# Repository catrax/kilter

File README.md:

# kilter
A compact multimode eurorack filter with MS-20 style resonance.
Filter core and resonance based on [René Schmitz' MS-20 schematic](https://www.schmitzbits.de/ms20.html).

# Features
- Voltage controlled filter with 4 simultaneous outputs:
	- 1-pole high pass
	- 2-pole low pass
	- 2-pole band pass (it's kind of an afterthought and needs to be improved, but it sounds okay)
	- 2-pole notch with adjustable depth (via trimmer on back)
- Two frequency CV inputs, one with an attenuverter
- Voltage controlled resonance with adjustable drive
- Two inputs with linear cross-fade
- 6HP

# Specifications
TODO: HP, power requirements, depth, input/output impedances and voltage ranges

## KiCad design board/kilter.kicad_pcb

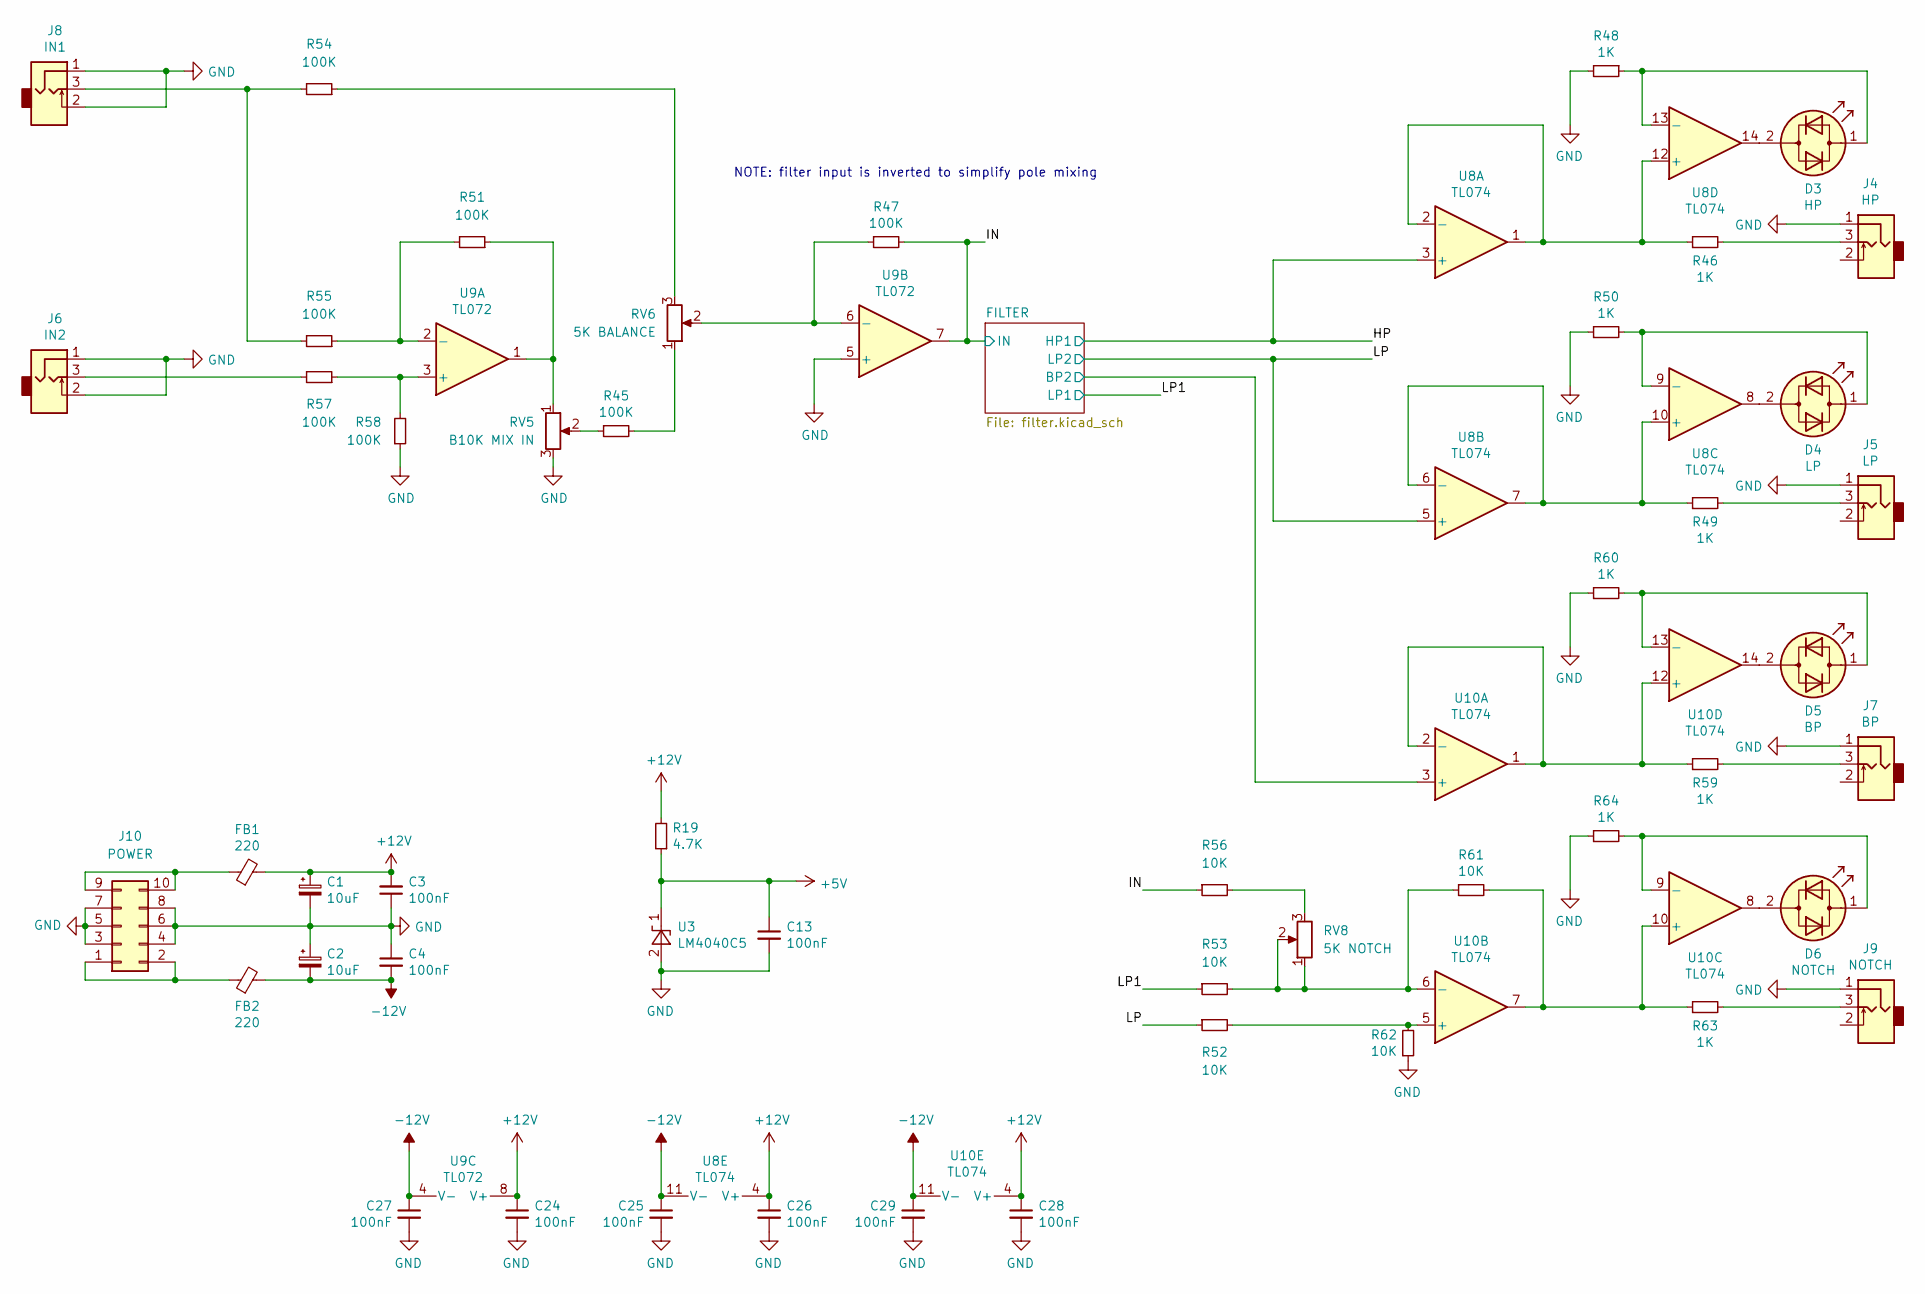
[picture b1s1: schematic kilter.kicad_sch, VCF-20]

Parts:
C1, C2: 10uF; CP_Elec_5x5.3; LCSC C178621
C3, C4, C13, C24, C25, C26, C27, C28, C29: 100nF; C_0603_1608Metric; LCSC C14663
D3: HP; LED_D3.0mm_Clear
D4: LP; LED_D3.0mm_Clear
D5: BP; LED_D3.0mm_Clear
D6: NOTCH; LED_D3.0mm_Clear
FB1, FB2: 220; R_0603_1608Metric; LCSC C88988
J4: HP; PJ301M
J5: LP; PJ301M
J6: IN2; PJ301M
J7: BP; PJ301M
J8: IN1; PJ301M
J9: NOTCH; PJ301M
J10: POWER; IDC-Header_2x05_P2.54mm_Vertical
R19: 4.7K; R_0603_1608Metric; LCSC C23162
R45, R47, R51, R54, R55, R57, R58: 100K; R_0603_1608Metric; LCSC C25803
R46, R48, R49, R50, R59, R60, R63, R64: 1K; R_0603_1608Metric; LCSC C21190
R52, R53, R56, R61, R62: 10K; R_0603_1608Metric; LCSC C25804
RV5: B10K MIX IN; Potentiometer_SongHuei_RD0904N-L25-KQ_Single_Vertical
RV6: 5K BALANCE; Potentiometer_Bourns_TC33X_Vertical; LCSC C719177
RV8: 5K NOTCH; Potentiometer_Bourns_TC33X_Vertical; LCSC C719177
U3: LM4040C5; SOT-23; LCSC C156291
U8, U10: TL074; TSSOP-14_4.4x5mm_P0.65mm; LCSC C96507
U9: TL072; TSSOP-8_4.4x3mm_P0.65mm; LCSC C90748

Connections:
+5V: C13.1, R19.1, U3.1 (K); also elsewhere on the board
+12V: C1.1, C3.2, C24.1, C26.1, C28.1, FB1.2, R19.2, U8.4 (V+), U9.8 (V+), U10.4 (V+); also elsewhere on the board
-12V: C2.2, C4.2, C25.1, C27.1, C29.1, FB2.2, U8.11 (V-), U9.4 (V-), U10.11 (V-); also elsewhere on the board
/FILTER/BP2: U10.3 (+); also elsewhere on the board
/HP: U8.3 (+); also elsewhere on the board
/IN: R47.2, R56.1, U9.7; also elsewhere on the board
/LP: R52.1, U8.5 (+); also elsewhere on the board
/LP1: R53.1; also elsewhere on the board
GND: C1.2, C2.1, C3.1, C4.1, C13.2, C24.2, C25.2, C26.2, C27.2, C28.2, C29.2, J4.1, J5.1, J6.1, J6.2, J7.1, J8.1, J8.2, J9.1, J10.3, J10.4, J10.5, J10.6, J10.7, J10.8, R48.2, R50.1, R58.1, R60.1, R62.1, R64.1, RV5.3, U3.2 (A), U9.5 (+); also elsewhere on the board
unnamed: D3.1 (KA), R48.1, U8.13 (-)
unnamed: D3.2 (AK), U8.14
unnamed: D4.1 (KA), R50.2, U8.9 (-)
unnamed: D4.2 (AK), U8.8
unnamed: D5.1 (KA), R60.2, U10.13 (-)
unnamed: D5.2 (AK), U10.14
unnamed: D6.1 (KA), R64.2, U10.9 (-)
unnamed: D6.2 (AK), U10.8
unnamed: FB1.1, J10.9, J10.10
unnamed: FB2.1, J10.1, J10.2
unnamed: J8.3, R54.2, R55.2
unnamed: J4.3, R46.2
unnamed: J6.3, R57.2
unnamed: J5.3, R49.2
unnamed: J7.3, R59.2
unnamed: J9.3, R63.2
unnamed: R51.1, RV5.1, U9.1
unnamed: R51.2, R55.1, U9.2 (-)
unnamed: R47.1, RV6.2, U9.6 (-)
unnamed: R46.1, U8.1, U8.2 (-), U8.12 (+)
unnamed: R57.1, R58.2, U9.3 (+)
unnamed: R45.1, RV5.2
unnamed: R45.2, RV6.1
unnamed: R49.1, U8.6 (-), U8.7, U8.10 (+)
unnamed: R59.1, U10.1, U10.2 (-), U10.12 (+)
unnamed: R53.2, R61.1, RV8.1, RV8.2, U10.6 (-)
unnamed: R61.2, R63.1, U10.7, U10.10 (+)
unnamed: R52.2, R62.2, U10.5 (+)
unnamed: R54.1, RV6.3
unnamed: R56.2, RV8.3

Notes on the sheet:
NOTE: filter input is inverted to simplify pole mixing

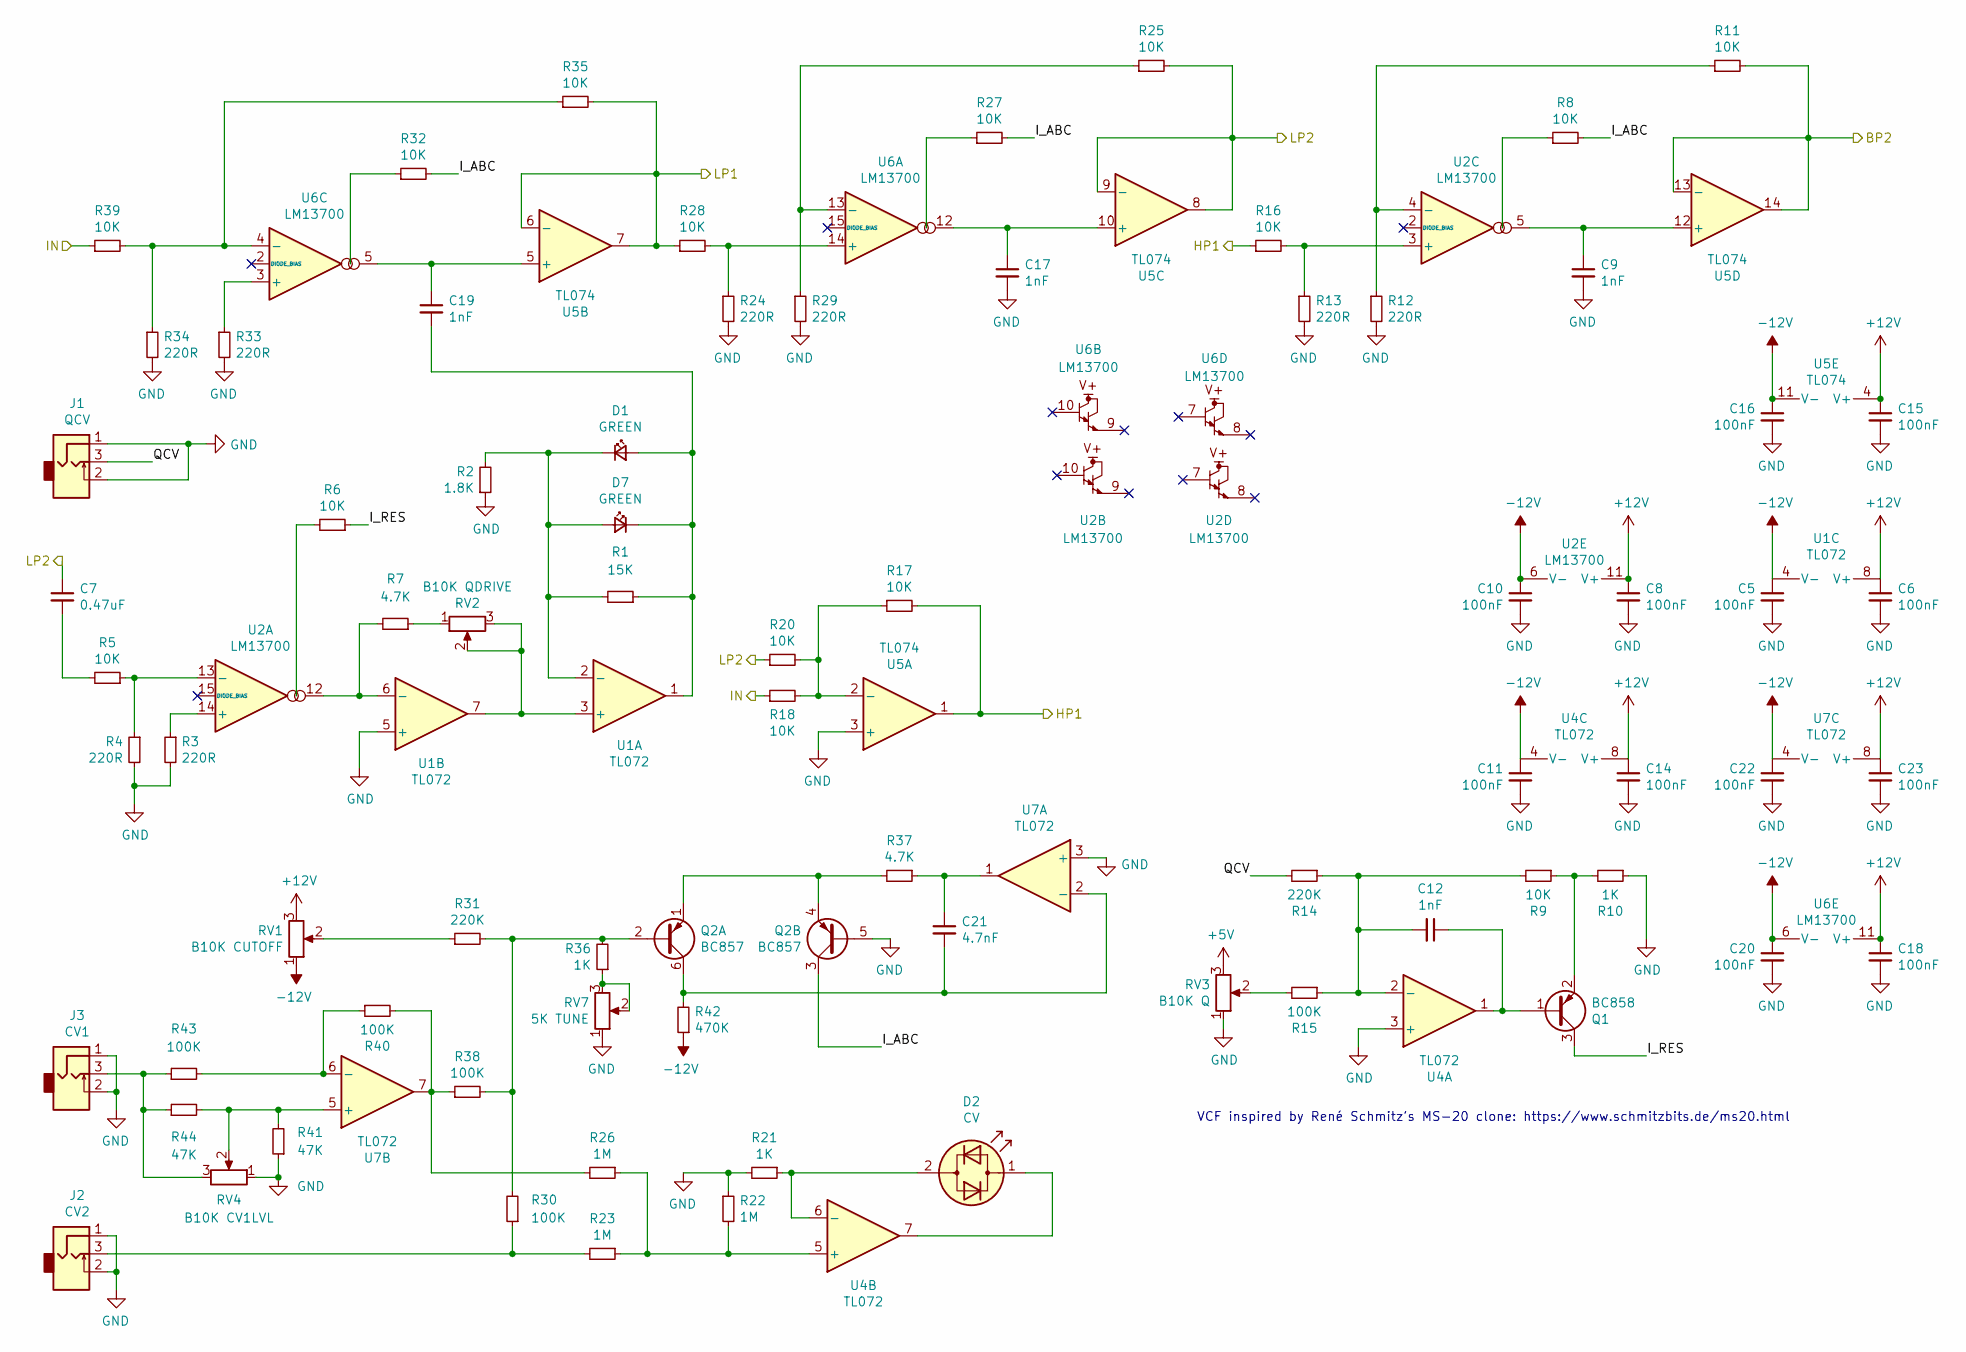
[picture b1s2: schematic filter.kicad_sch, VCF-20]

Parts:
C5, C6, C8, C10, C11, C14, C15, C16, C18, C20, C22, C23: 100nF; C_0603_1608Metric; LCSC C14663
C7: 0.47uF; C_0603_1608Metric; LCSC C1623
C9, C12, C17, C19: 1nF; C_0603_1608Metric; LCSC C1588
C21: 4.7nF; C_0603_1608Metric; LCSC C338071
D1, D7: GREEN; LED_D3.0mm
D2: CV; LED_D3.0mm_Clear
J1: QCV; PJ301M
J2: CV2; PJ301M
J3: CV1; PJ301M
Q1: BC858; SOT-23; LCSC C596216
Q2: BC857; SOT-363_SC-70-6; LCSC C105887
R1: 15K; R_0603_1608Metric; LCSC C22809
R2: 1.8K; R_0603_1608Metric; LCSC C4177
R3, R4, R12, R13, R24, R29, R33, R34: 220R; R_0603_1608Metric; LCSC C22962
R5, R6, R8, R9, R11, R16, R17, R18, R20, R25, R27, R28, R32, R35, R39: 10K; R_0603_1608Metric; LCSC C25804
R7, R37: 4.7K; R_0603_1608Metric; LCSC C23162
R10, R21, R36: 1K; R_0603_1608Metric; LCSC C21190
R14, R31: 220K; R_0603_1608Metric; LCSC C22961
R15, R30, R38, R40, R43: 100K; R_0603_1608Metric; LCSC C25803
R22, R23, R26: 1M; R_0603_1608Metric; LCSC C22935
R41, R44: 47K; R_0603_1608Metric; LCSC C25819
R42: 470K; R_0603_1608Metric; LCSC C23178
RV1: B10K CUTOFF; Potentiometer_Alpha_RD901F-40-00D_Single_Vertical
RV2: B10K QDRIVE; Potentiometer_SongHuei_RD0904N-L25-KQ_Single_Vertical
RV3: B10K Q; Potentiometer_Alpha_RD901F-40-00D_Single_Vertical
RV4: B10K CV1LVL; Potentiometer_Alpha_RD901F-40-00D_Single_Vertical
RV7: 5K TUNE; Potentiometer_Bourns_TC33X_Vertical; LCSC C719177
U1, U4, U7: TL072; TSSOP-8_4.4x3mm_P0.65mm; LCSC C90748
U2, U6: LM13700; SOIC-16_3.9x9.9mm_P1.27mm; LCSC C174050
U5: TL074; TSSOP-14_4.4x5mm_P0.65mm; LCSC C96507

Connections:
+5V: RV3.3; also elsewhere on the board
+12V: C6.1, C8.1, C14.1, C15.1, C18.1, C23.1, RV1.3, U1.8 (V+), U2.11 (V+), U4.8 (V+), U5.4 (V+), U6.11 (V+), U7.8 (V+); also elsewhere on the board
-12V: C5.1, C10.1, C11.1, C16.1, C20.1, C22.1, R42.1, RV1.1, U1.4 (V-), U2.6 (V-), U4.4 (V-), U5.11 (V-), U6.6 (V-), U7.4 (V-); also elsewhere on the board
/FILTER/BP2: R11.2, U5.13 (-), U5.14; also elsewhere on the board
/FILTER/I_ABC: Q2.3 (C2), R8.2, R27.2, R32.2
/FILTER/I_RES: Q1.3 (C), R6.1
/FILTER/QCV: J1.3, R14.2
/HP: R16.1, R17.2, U5.1; also elsewhere on the board
/IN: R18.1, R39.1; also elsewhere on the board
/LP: C7.1, R20.1, R25.2, U5.8, U5.9 (-); also elsewhere on the board
/LP1: R28.1, R35.2, U5.6 (-), U5.7; also elsewhere on the board
GND: C5.2, C6.2, C8.2, C9.2, C10.2, C11.2, C14.2, C15.2, C16.2, C17.2, C18.2, C20.2, C22.2, C23.2, J1.1, J1.2, J2.1, J2.2, J3.1, J3.2, Q2.5 (B2), R2.1, R3.2, R4.2, R10.1, R12.2, R13.2, R21.2, R22.1, R24.2, R29.2, R33.2, R34.2, R41.1, RV3.1, RV4.1, RV7.1, U1.5 (+), U4.3 (+), U5.3 (+), U7.3 (+); also elsewhere on the board
unnamed: C17.1, U5.10 (+), U6.12
unnamed: C9.1, U2.5, U5.12 (+)
unnamed: C19.1, U5.5 (+), U6.5
unnamed: C19.2, D1.2 (A), D7.1 (K), R1.1, U1.1
unnamed: C7.2, R5.2
unnamed: C21.1, R37.1, U7.1
unnamed: C21.2, Q2.6 (C1), R42.2, U7.2 (-)
unnamed: C12.1, Q1.1 (B), U4.1
unnamed: C12.2, R9.2, R14.1, R15.1, U4.2 (-)
unnamed: D1.1 (K), D7.2 (A), R1.2, R2.2, U1.2 (-)
unnamed: D2.1 (KA), U4.7
unnamed: D2.2 (AK), R21.1, U4.6 (-)
unnamed: J3.3, R43.1, R44.1, RV4.3
unnamed: J2.3, R23.2, R30.1
unnamed: Q2.1 (E1), Q2.4 (E2), R37.2
unnamed: Q2.2 (B1), R30.2, R31.2, R36.2, R38.2
unnamed: Q1.2 (E), R9.1, R10.2
unnamed: R25.1, R29.1, U6.13 (-)
unnamed: R11.1, R12.1, U2.4 (-)
unnamed: R34.1, R35.1, R39.2, U6.4 (-)
unnamed: R27.1, U6.16
unnamed: R8.1, U2.1
unnamed: R32.1, U6.1
unnamed: R24.1, R28.2, U6.14 (+)
unnamed: R13.1, R16.2, U2.3 (+)
unnamed: R33.1, U6.3 (+)
unnamed: R17.1, R18.2, R20.2, U5.2 (-)
unnamed: R6.2, U2.16
unnamed: R4.1, R5.1, U2.13 (-)
unnamed: R3.1, U2.14 (+)
unnamed: R31.1, RV1.2
unnamed: R36.1, RV7.2, RV7.3
unnamed: R15.2, RV3.2
unnamed: R26.2, R38.1, R40.2, U7.7
unnamed: R41.2, R44.2, RV4.2, U7.5 (+)
unnamed: R40.1, R43.2, U7.6 (-)
unnamed: R22.2, R23.1, R26.1, U4.5 (+)
unnamed: R7.1, RV2.1
unnamed: R7.2, U1.6 (-), U2.12
unnamed: RV2.2, RV2.3, U1.3 (+), U1.7

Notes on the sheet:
VCF inspired by René Schmitz's MS-20 clone: https://www.schmitzbits.de/ms20.html

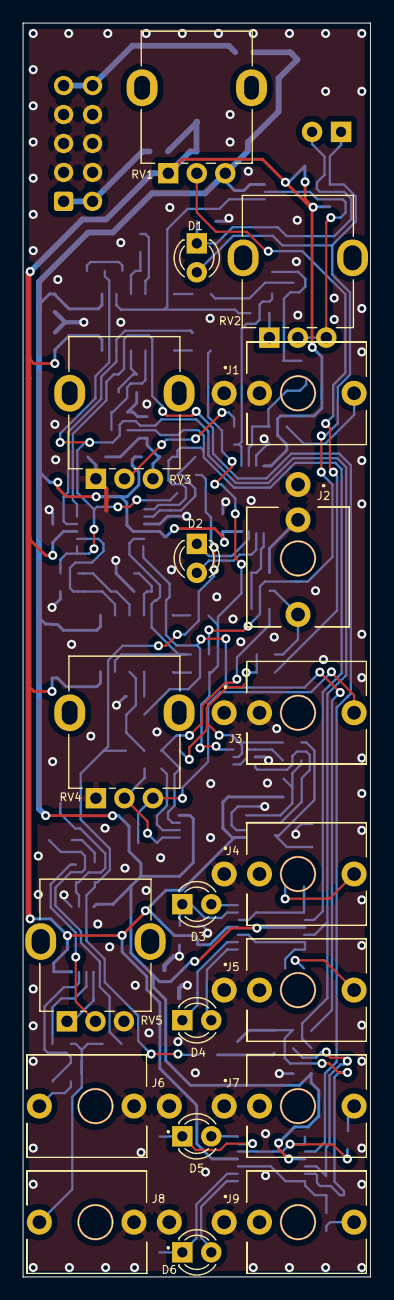
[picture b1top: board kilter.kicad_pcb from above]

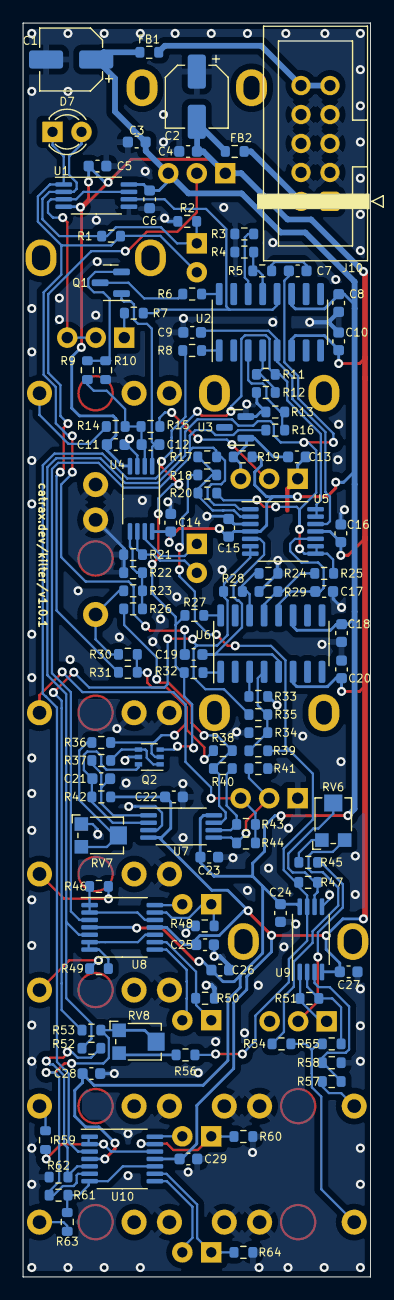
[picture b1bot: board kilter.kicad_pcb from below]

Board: 2 copper layers, 30.5 x 110.0 mm, 132 parts (112 on the bottom side), 82 nets.

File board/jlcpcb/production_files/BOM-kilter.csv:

Comment,Designator,Footprint,LCSC
BC857,Q2,SOT-363_SC-70-6,C105887
100nF,"C10,C11,C13,C14,C15,C16,C18,C20,C22,C23,C24,C25,C26,C27,C28,C29,C3,C4,C5,C6,C8",C_0603_1608Metric,C14663
LM4040C5,U3,SOT-23,C156291
1nF,"C12,C17,C19,C9",C_0603_1608Metric,C1588
0.47uF,C7,C_0603_1608Metric,C1623
LM13700,"U2,U6",SOIC-16_3.9x9.9mm_P1.27mm,C174050
10uF,"C1,C2",CP_Elec_5x5.3,C178621
1K,"R10,R21,R36,R46,R48,R49,R50,R59,R60,R63,R64",R_0603_1608Metric,C21190
15K,R1,R_0603_1608Metric,C22809
1M,"R22,R23,R26",R_0603_1608Metric,C22935
220K,"R14,R31",R_0603_1608Metric,C22961
220R,"R12,R13,R24,R29,R3,R33,R34,R4",R_0603_1608Metric,C22962
4.7K,"R19,R37,R7",R_0603_1608Metric,C23162
470K,R42,R_0603_1608Metric,C23178
100K,"R15,R30,R38,R40,R43,R45,R47,R51,R54,R55,R57,R58",R_0603_1608Metric,C25803
10K,"R11,R16,R17,R18,R20,R25,R27,R28,R32,R35,R39,R5,R52,R53,R56,R6,R61,R62,R8,R9",R_0603_1608Metric,C25804
47K,"R41,R44",R_0603_1608Metric,C25819
4.7nF,C21,C_0603_1608Metric,C338071
1.8K,R2,R_0603_1608Metric,C4177
BC858,Q1,SOT-23,C596216
5K BALANCE,"RV6,RV7,RV8",Potentiometer_Bourns_TC33X_Vertical,C719177
220,"FB1,FB2",R_0603_1608Metric,C88988
TL072,"U1,U4,U7,U9",TSSOP-8_4.4x3mm_P0.65mm,C90748
TL074,"U10,U5,U8",TSSOP-14_4.4x5mm_P0.65mm,C96507
B10K QDRIVE,RV2,Potentiometer_SongHuei_RD0904N-L25-KQ_Single_Vertical,
B10K CV1LVL,RV4,Potentiometer_Alpha_RD901F-40-00D_Single_Vertical,
GREEN,D1,LED_D3.0mm,
CV2,J2,PJ301M,
QCV,J1,PJ301M,
CV,D2,LED_D3.0mm_Clear,
HP,D3,LED_D3.0mm_Clear,
LP,D4,LED_D3.0mm_Clear,
BP,D5,LED_D3.0mm_Clear,
CV1,J3,PJ301M,
HP,J4,PJ301M,
LP,J5,PJ301M,
BP,J7,PJ301M,
IN1,J8,PJ301M,
NOTCH,J9,PJ301M,
POWER,J10,IDC-Header_2x05_P2.54mm_Vertical,
GREEN,D7,LED_D3.0mm,
IN2,J6,PJ301M,
NOTCH,D6,LED_D3.0mm_Clear,
B10K CUTOFF,RV1,Potentiometer_Alpha_RD901F-40-00D_Single_Vertical,
B10K Q,RV3,Potentiometer_Alpha_RD901F-40-00D_Single_Vertical,
B10K MIX IN,RV5,Potentiometer_SongHuei_RD0904N-L25-KQ_Single_Vertical,

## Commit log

2020-08-22 Initial commit of existing v0.1 design
2020-08-22 Add readme
2020-09-01 Update schematic with resonance and crossfader fixes
2020-11-08 Redesign filter core and revise board layout
2020-11-08 Partially update README
2020-11-08 Update README again
2022-05-18 Add panel, plus some minor fixes to crossfade and resonance drive
2022-05-18 Fix image size in README
2022-12-27 fix crossfade and notch; improve attenuverter
2022-12-27 rename project
2022-12-27 Fix mounting holes for tall trimmer pots
2022-12-27 Fix reference designator rotations
2022-12-29 Update panel and add jlcpcb assembly files
2023-02-25 fix resonance gain and simplify module calibration
2023-02-26 fix back silkscreen and update production files
